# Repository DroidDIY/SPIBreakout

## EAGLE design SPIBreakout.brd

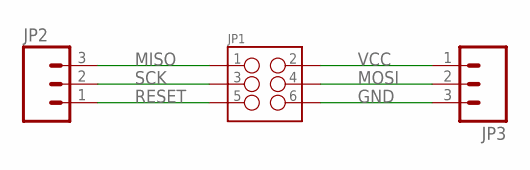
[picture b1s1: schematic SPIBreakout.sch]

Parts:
JP1: M03X2FEMALE; 2X3
JP2, JP3: M03PTH; 1X03

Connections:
GND: JP1.6, JP3.3
MISO: JP1.1, JP2.3
MOSI: JP1.4, JP3.2
RESET: JP1.5, JP2.1
SCK: JP1.3, JP2.2
VCC: JP1.2, JP3.1

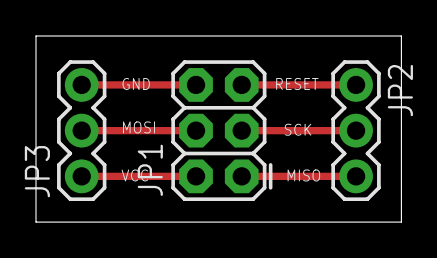
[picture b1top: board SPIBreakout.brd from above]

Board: 2 copper layers, 20.3 x 10.3 mm, 3 parts (0 on the bottom side), 6 nets.

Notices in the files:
parts and their libraries:
SparkFun-Connectors: Licensing: Creative Commons ShareAlike 4.0 International - https://creativecommons.org/licenses/by-sa/4.0
